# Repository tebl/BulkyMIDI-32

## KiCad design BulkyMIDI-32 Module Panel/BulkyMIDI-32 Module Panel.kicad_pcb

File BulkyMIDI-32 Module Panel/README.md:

# BulkyMIDI-32 Module Panel
This is a front-facing panel for controlling the *BulkyMIDI-32 Module*, while optional by design I find that it makes the system a lot more enjoyable in use and looks better while on my desk.

- [1> Building the device](#1-building-the-device)
  - [1.1> Soldering it together](#11-soldering-it-together)
- [2> Schematic](#2-schematic)
- [3> BOM](#3-bom)

# 1> Building the device
Building a device such as this assumes you have at least minor experience soldering things together, recommended is that you at the very least have access to a soldering station with adjustable temperature. If currently available, you should probably start with 60/40 rosin core solder as the lead-free alternatives tends to be a bit harder to work with.

With requirements for basic equipment sorted, we need to talk a bit about what you want to achieve while building this project. The reason I ask is that while you can build a functional *mt32-pi* using the module alone, you can also build the complete version of it - including front panels, faceplates that goes on the top as well as *extras*-module for additional functionality. 

Now that you know what you want to build, we can get started on the most expensive step in any build process - shopping! So, head on over to the [BOM](#3-bom)-section for some information on what kind of components that you'll need. While I would have liked to give you specific part numbers for "reputable" electronic part suppliers, I can't afford to shop there so I usually make due with what I can find on sites such as ebay, AliExpress and any similar sites that sell cheap chinese components. The downside to this is that I can't link to a part directly and expect it to stay listed, so you'll need to consider the description listed as suggested search terms.

## 1.1> Soldering it together

The construction of this unit should be fairly straight-forward, just take your time in order to make sure everything goes into place - more or less straight. I usually recommend starting by having a good look at the PCBs, try to figure out where all of the listed components go and in which orientation they go in (all of this should be clearly marked on the silkscreen). 

The first component to install might be a bit backwards to normal convention, but I've started wth the 8mm hex standoffs. The hex shape needs to be rotated a flat edge lines up with the left and right edges of the PCB, the reason for this will become evident when we attempt to install it onto the main module. As these are just nylon, I've made things slightly easier for myself by using a sharp knife to trim a bit off the vertical edges of them - in particular the one sitting just above the power LED.

As the next step, I've skipped a bit too far ahead and simply added everything - starting with the right-angle pin headers that will be mounted on the backside of the PCB. The alignment of the remaining components need to be perfectly straight, so my recommendation is to insert them roughly into place then mount the [front plate](https://github.com/tebl/BulkyMIDI-32/tree/main/faceplates/BulkyMIDI-32%20Module%20FP1) on the top of it. A single pin of each component is then soldered, check the alignment and then reheat and adjust as needed. I prefer to push the LED slightly from the back to ensure that it is sitting flush against the front plate.

The front panel would then been removed again, mostly because it'll slightly be in the way when installing it onto the main [BulkyMIDI-32](https://github.com/tebl/BulkyMIDI-32/tree/main/BulkyMIDI-32%20Module) PCB. Before continuing we need to deal with the solder jumbers found on the back, these are divided into two sets of jumpers that need to be added.

The first pair marked **JP1/JP2** control the scroll direction of the rotary encoder, but for the most part you'd just solder both of these across pins *1-2* (the little triangle denotes pin 1). This should be fine for most of the rotary encoders that I've encountered, but in the case that they will appear to work backwards from what you expect - then move the solder bridge to pins *2-3* instead.

Next we need to deal with **JP3/JP4**, these are used to deal with the rather unfortunate situation caused by some manufacturers making changes to the pinout. Particularly this is a problem with 0.96" OLED displays, often you'll order a display based on the picture in the listing and receive a display with a different pinout than that of what you had ordered. The only way around it is to ensure that we handle that on our end of the hardware, for the specific display shown above you can see thet the first pin has been marked *GND* - for that reason we need to solder both jumpers across pins *1-2* (the little triangle denotes pin 1). If on the hand, *VCC* had been the first pin then we would instead need to solder both across pins *2-3*. Preferably double-check and triple-check this before continuing as the wrong setting will commonly destroy the display module.

The actual installation of the display needs to be oriented perfectly against the front panel, but that part of the build details will be handled as part of the [build instructions](https://github.com/tebl/BulkyMIDI-32/blob/main/BulkyMIDI-32%20Module/README.md#132-front-panel) for the [main](https://github.com/tebl/BulkyMIDI-32/tree/main/BulkyMIDI-32%20Module) module.

# 2> Schematic
The supplied KiCad files should be sufficient as both a schematic and as a  starting point for ordering PCBs (basically you could just zip the contents of the export folder and upload that on a fabrication site), the schematic is also available in [PDF-format](https://github.com/tebl/BulkyMIDI-32/tree/main/documentation/schematic) and this is what you'll need to print and work your way through this things don't work as expected after assembly.

# 3> BOM
Most parts should be easy to get a hold of from your favourite local electronic component shop, but given that I don't have access to such shops where I live so everything was based on whatever I could get cheapest from eBay/AliExpress (free shipping, but plan on waiting 3-4 weeks for delivery). Components in parenthesis can be considered optional for features beyond the more basic functionality, but where's the fun in that? You deserve the complete package.

| Reference             | Item                                                              | Count | Order  |
| --------------------- | ----------------------------------------------------------------- | ----- | ------ |
| Panel PCB             | Fabricate using Gerber files                                      |     1 | [PCBWay](https://www.pcbway.com/project/shareproject/BulkyMIDI_32_Module_Panel_17b7fa7c.html)
| D1                    | 5mm LEDs, preferably frosted (not the bright clear ones)          |     1 |
| ENC1                  | EC11 rotary encoder, 20mm. Preferably plum handle                 |     1 |
| IC1                   | 1.3 inch I2C OLED display (can use 0.96 inch display as well)     |     1 |
| J1                    | Breakable right-angle pin header                                  |     1 |
| SW1,SW2               | 6x6x12mm momentary button                                         |     2 |
| Mounting ****         | Nylon M3 hex standoffs 8mm (M-F)                                  |     4 |
| Mounting ****         | Nylon M3x6mm nylon screws                                         |     4 |
| Mounting ****         | Nylon M3x6mm nylon nuts                                           |     4 |

****) These are available in the form of kits usually advertised *M3 nylon standoff kit* which should contain most of what you'd need. I do however recommend that you pick up extra M-F standoffs of lengths 8mm and 20mm, as quite a lot of them will be used when building more than one module.

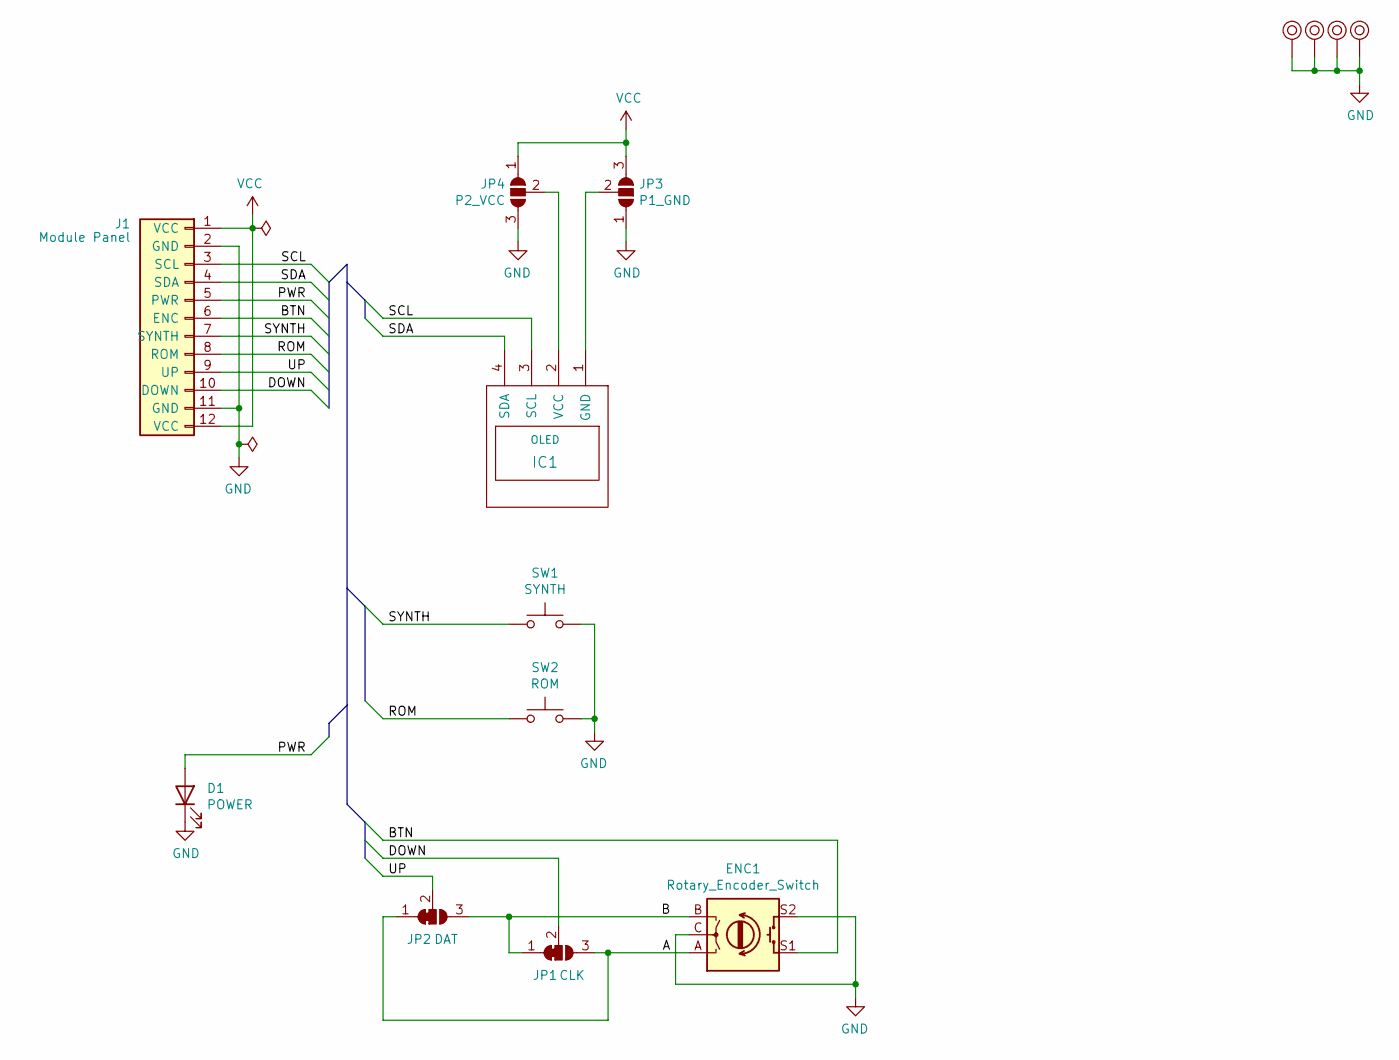
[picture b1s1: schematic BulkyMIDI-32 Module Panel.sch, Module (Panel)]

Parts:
D1: POWER; LED_D5.0mm
ENC1: Rotary_Encoder_Switch; RotaryEncoder_Alps_EC11E-Switch_Vertical_H20mm
IC1: OLED; 1.3_I2C_OLED_No_mounting
J1: Module Panel; PinHeader_1x12_P2.54mm_Horizontal
JP1: CLK; SolderJumper-3_P1.3mm_Open_Pad1.0x1.5mm
JP2: DAT; SolderJumper-3_P1.3mm_Open_Pad1.0x1.5mm
JP3: P1_GND; SolderJumper-3_P1.3mm_Open_Pad1.0x1.5mm
JP4: P2_VCC; SolderJumper-3_P1.3mm_Open_Pad1.0x1.5mm
M1, M2, M3, M4: Mounting_Pin; M3_pin
SW1: SYNTH; SW_PUSH_6mm
SW2: ROM; SW_PUSH_6mm

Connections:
/A: ENC1.A, JP1.3 (B), JP2.1 (A)
/B: ENC1.B, JP1.1 (A), JP2.3 (B)
/BTN: ENC1.S1, J1.6 (ENC)
/DOWN: J1.10 (DOWN), JP1.2 (C)
/PWR: D1.2 (A), J1.5 (PWR)
/ROM: J1.8 (ROM), SW2.1
/SCL: IC1.3 (SCL), J1.3 (SCL)
/SDA: IC1.4 (SDA), J1.4 (SDA)
/SYNTH: J1.7 (SYNTH), SW1.1
/UP: J1.9 (UP), JP2.2 (C)
GND: D1.1 (K), ENC1.C, ENC1.S2, J1.2 (GND), J1.11 (GND), JP3.1 (A), JP4.3 (B), M1.1, M2.1, M3.1, M4.1, SW1.2, SW2.2
unnamed: IC1.1 (GND), JP3.2 (C)
unnamed: IC1.2 (VCC), JP4.2 (C)
VCC: J1.1 (VCC), J1.12 (VCC), JP3.3 (B), JP4.1 (A)

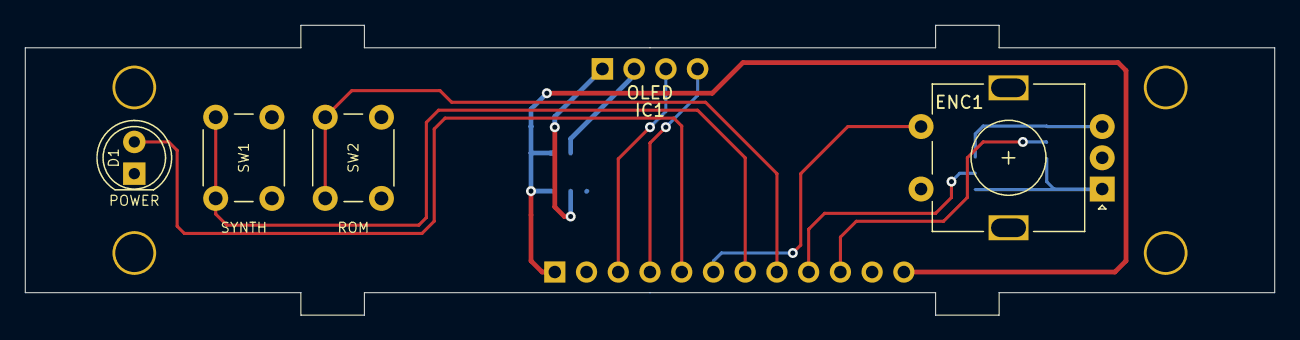
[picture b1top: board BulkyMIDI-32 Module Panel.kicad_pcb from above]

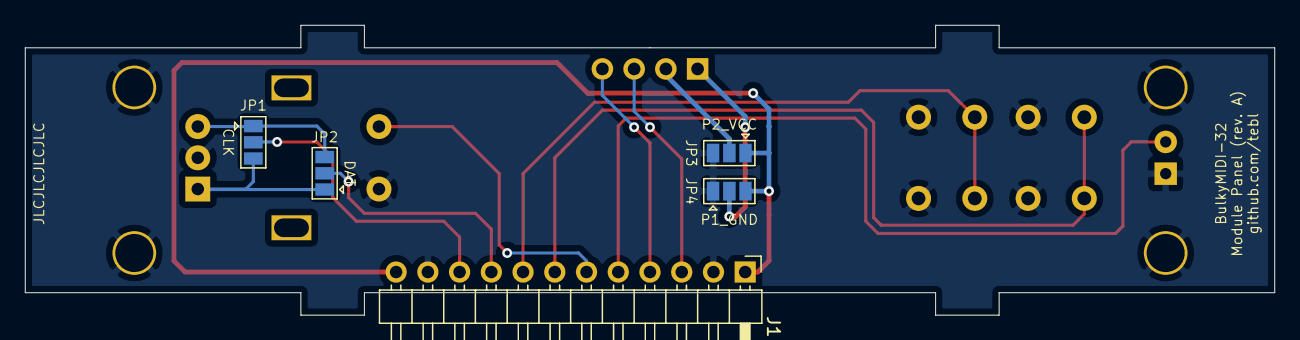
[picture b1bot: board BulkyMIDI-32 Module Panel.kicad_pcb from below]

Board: 2 copper layers, 100.0 x 23.2 mm, 14 parts (5 on the bottom side), 14 nets.

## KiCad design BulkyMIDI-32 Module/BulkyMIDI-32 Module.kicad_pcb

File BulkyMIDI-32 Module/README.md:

# BulkyMIDI-32 Module
The complete BulkyMIDI-32 consists of several separate PCB designs, this documentation covers the main module that enables you to use common functionality supported by the [mt32-pi](https://github.com/dwhinham/mt32-pi) firmware. Any additional modules such as the [BulkyMIDI-32 Extras](https://github.com/tebl/BulkyMIDI-32/tree/main/BulkyMIDI-32%20Extras), will have their own set of documenentation - so make sure that you browse around to get the full picture (especially while ordering parts).

- [1> Building the device](#1-building-the-device)
  - [1.1> Soldering it together](#11-soldering-it-together)
  - [1.2> I2S DAC](#12-i2s-dac)
  - [1.3> User interface](#13-user-interface)
    - [1.3.1> Basic interface](#131-basic-interface)
      - [1.3.1.1> Mounting the screen](#1311-mounting-the-screen)
    - [1.3.2> Front panel](#132-front-panel)
  - [1.4> Adding connectors](#14-adding-connectors)
  - [1.5> Finishing touches](#15-finishing-touches)
- [2> Schematic](#2-schematic)
- [3> BOM](#3-bom)

# 1> Building the device
Building a device such as this assumes you have at least minor experience soldering things together, recommended is that you at the very least have access to a soldering station with adjustable temperature. If currently available, you should probably start with 60/40 rosin core solder as the lead-free alternatives tends to be a bit harder to work with.

With requirements for basic equipment sorted, we need to talk a bit about what you want to achieve while building this project. The reason I ask is that while you can build a functional *mt32-pi* using the module alone, you can also build the complete version of it - including front panels, faceplates that goes on the top as well as *extras*-module for additional functionality. 

Now that you know what you want to build, we can get started on the most expensive step in any build process - shopping! So, head on over to the [BOM](#3-bom)-section for some information on what kind of components that you'll need. While I would have liked to give you specific part numbers for "reputable" electronic part suppliers, I can't afford to shop there so I usually make due with what I can find on sites such as ebay, AliExpress and any similar sites that sell cheap chinese components. The downside to this is that I can't link to a part directly and expect it to stay listed, so you'll need to consider the description listed as suggested search terms.

While you wait for the parts to arrive, feel free to have a look at the introduction video - going into what the Roland MT-32 is and why you would want one. Also covers MIDI and where the MT32-PI software comes into all of this. 

## 1.1> Soldering it together
The construction of this unit should be fairly straight-forward, just take your time in order to make sure everything goes into place - more or less straight. To aid you in the process I've put together a video showing most of these parts in detail, but feel free to skip forward to the various chapters if you feel unsure about things.

I usually recommend starting by having a good look at the PCBs, try to figure out where all of the listed components go and in which orientation they go in (all of this should be clearly marked on the silkscreen). 

I will usually try to install components sorted by their physical size, doing it this way means you'll have an easier time keeping everything from looking somewhat crooked. This is your board, your build and you want it perfect - don't you? If you said no, then go sit in the corner because I worked hard on creating this for myself and whoever wants to build one.

Here we've started by soldering all of the resistors, ensuring that we're using the correct values in each position. The single 1n4148 diode has also been installed, pay particular attention that the black band of the components matches up with the markings on the PCB.

Sockets should be installed for the two ICs needed for the complete unit - you could probably manage without them if you know that you're using known good parts. However, they're cheap and you could probably afford to be quite so *cheap*!  I recommend tacking opposing corners into place, then reheat and push flush against the board before soldering the remaining pins.

We've also gone ahead and installed our non-polarized capacitors - they should in theory be something called an *X7R* or *film* capacitors. I don't have any of those, so I just used the regular stuff I have around the workshop instead (it'll be fine - I probably wouldn't be able to tell the difference anyway).  

Next step is adding the female 40-pin header, this is where we'll be plugging in our Raspberry Pi 3 or 4 - sometime in the future.

Speaking of capacitors, we'll just go ahead and install the polarized ones as well - of which, there are 10 (unless my counting is *off* or outdated, that's two in binary). As polarized as they are, we need to ensure that these are installed the right way around - the stripe on the side of the capacitor denotes the negative side of it (not the correct term I fear) and this should match the filled in area on the footprint. When in doubt, the longer pin goes into the other hole (the one marked with a "+").

Also added is your common DC barrel connector (5.5mm x 2.1mm), these are notorious for going in crooked so make sure to only solder one pin to get started. Reheat and adjust until perfectly satisfied with the result, then solder in the remaining pins before continuing.

## 1.2> I2S DAC
If you've ever attempted to use a Raspberry Pi module as some sort of desktop solution, you may already have noticed the rather horrible audio quality coming out of its audio jack. For this reason alone, we need to include a separate DAC as part of the design. While there are a few variants on sale, the one that is compatible with this design is listed as a *GY-PCM5102*-module - commonly found on ebay, AliExpress and places known for cheap components. When in doubt, look for the colour purple among when the store listings.

There are a set of solder jumpers on the underside, you need to check that these are set up according to what is shown above. These'll be inaccessible after solder the modules together, so this is definitely the time for checking it twice. H3L should be linked in the left position, the remaining in the right position. I've also gone ahead and added the pin headers to the board.

Here we've just gone ahead and soldered it to the main board. On the underside there are some solder bridges that can be added, these'll send the analog audio signal to the extras board connector. Personally I just solder them so that they're ready for the extras board - sound aficionados may appreciate the option not to, but again I just wasn't able to detect any difference.

## 1.3> User interface
The user interface can be added to the *BulkyMIDI-32* in several ways though at the moment only two variants will be covered. The first one, covering basic interface functionality, is intended for putting together a cheaper version - only requiring this module. The second is the more stylish and feature-complete version of the *BulkyMIDI-32*, this mounts all of the buttons as well as the display on a separate [front panel](https://github.com/tebl/BulkyMIDI-32/tree/main/BulkyMIDI-32%20Module%20Panel)-module. 

- [1.3.1> Basic interface](#131-basic-interface)
  - [1.3.1.1> Mounting the screen](#1311-mounting-the-screen)
- [1.3.2> Front panel](#132-front-panel)

### 1.3.1> Basic interface
**WARNING!** The pictures for this section are outdated, but as long as you follow the descriptions you'll find that although the position of the components have been moved around to put the display in the middle of the device. Despite this, the process should be comparable.

When you want to build a simpler version of the *BulkyMIDI-32*, the switches will be installed directly on the module as one would expect. This configuration requires that you link **SW4_SEL** pins **1-2** on the back of the PCB as well.

**NB!** If you've already built a previous version of the [extras](https://github.com/tebl/BulkyMIDI-32/tree/main/BulkyMIDI-32%20Extras)-board the separate adapter board for the rotary encoder, then you can choose to skip the installation of *volume up* and the *volume down* switches.

#### 1.3.1.1> Mounting the screen
For this project you can use the standard 0.96 inch I2C OLED displays available from just about anyone who peddles in Arduino modules, but as a I wanted a bit more flair I instead opted to install a 1.3 inch display. They have a mostly compatible display chip driving it, offering the same amount of pixels - each pixel is just slightly bigger.

**WARNING!** One thing you need to take note of is the organization of the pins, in this case GND is pin 1. Especially the 0.96 inch displays seems to randomly come with the GND and VCC pins swapped around, meaning that if you're not careful - you'll easily destroy the display! We'll cover all of that though, so no worries as long as you follow the instructions.

It's not all that easy to spot in this picture as the display was recycled from an earlier project of mine, but the key to accurately mounting the display somewhat straight is that I've used the long variety of pin headers - they're made of a softer metal and easily bent into the correct position for the display. As some of the backing will be sitting up almost up against the Raspberry Pi, I've added some tape to the back as well in order to avoid any unintended accidents.

Remember when I mentioned earlier about wiring up the display correct? This is where you do that. When viewed from the front, the display pictured has GND as the first pin. To wire up this correctly, there are a couple of solder bridges near the display connector that we need to link correctly. Given this display, we short across pins **1-2** (the little arrow marking pin 1) for the both of them. If on the other hand, you had VCC as the first pin - then you'd instead link pins **2-3**.

If you've chosen to build a basic unit with the faceplate, then this is probably a good time to get that installed on there - mainly as it'll act as a guide when mounting the display. Turning the display upside down as pictured, insert the pins into the holes and gently bend the pins until you get an orientation that looks somewhat straight. Solder the outside pins into place, reheat and reorient the display until you're happy with the end result. Solder into place the two remaining pins before continuing.

### 1.3.2> Front panel
This section assumes that you've chosen to install a front panel for use with the *BulkyMIDI-32*, this is a bit more advanced way of installing the components for the user interface (switches, OLED-screen and rotary encoder). Building up the [front panel](https://github.com/tebl/BulkyMIDI-32/tree/main/BulkyMIDI-32%20Module%20Panel) in details will be covered by its own documentation, but as it is closely designed for use with this module - some of the information may be duplicated between the two documents. 

A front panel that has been prepared for installing on the module is shown above, in particular you should note that a display has not yet been installed. The reason for this is that we need to get the alignment correct.

Looking at the front panel you've probably noticed that there are some tabs sticking out, these have been designed so that they slot into the main module as well as the faceplates that go on top. The purpose of these is so that every time you're pressing the buttons, you aren't simply bending a comparatively weak set of pin headers that'll be poking through the board. Without soldering anything, insert it into place and fix the faceplate temporarily into place.

If it feels like any of the boards want to bend or not sit straight, check the alignment of the hex standoffs so that they match you can barely see in the picture above. The clue here is that the two sets of standoffs, both the horizontal and the vertical ones need to have a flat side towards eachother - depending on the production of the components you may need to shave a bit off the edge pointing directly up and down to give them a bit more room. I had some issues where the tabs lacked a sharp edge and was binding against the cutout in the boards, these can be cleaned up using a sharp knife (in particular I had this issue when it was produced by JLCPCB as compared to PCBWay). When satisfied with the alignment, you can finally solder the two boards together.

I'm not going to cover the installation of the display in great details, as that would be duplicating a significant portion of the documentation for the [front panel](https://github.com/tebl/BulkyMIDI-32/tree/main/BulkyMIDI-32%20Module%20Panel). In particular there are couple of solder bridges on the back that need to be set up correctly to match the display you're using. Not paying attention to this step will kill your display, at best it simply won't work.

The display should have had some standard pin headers added to them, then simply insert the pins into the front panel without soldering. Add the [front panel faceplate](https://github.com/tebl/BulkyMIDI-32/tree/main/faceplates/BulkyMIDI-32%20Module%20FP1) using screws, allowing the display to flop around between the two front panel boards. Orient the display as correctly as you can, then solder one of the pins into place - reaheat and move it around as needed until you're happy with it it - the display should be straight when viewed from the front window, it should also be mostly flush against it. Solder the remaining pins to finish the installation.

## 1.4> Adding connectors
The number of connectors needed would depend on what you want, but I recommend adding both of the 5-pin DIN connectors to the board - the left one is used with data into the device, more than likely this is either your computer with a suitable MIDI-adapter or a keyboard. The right one is for MIDI-output from the device, mostly when you want to chain it to other MIDI-devices.

One slightly annoying part of using these female connectors with the Raspberry Pi is that the height between the two boards will be around 11mm, which is mainly just a problem because I've not seen a vendor selling a cheap one that is this height (plenty of 8mm, 10mm and 12mm standoffs to go around). We could simply just leave it hanging there, but with the prices of these boards we can't do that. Not even close. Luckily, the standoffs have just about enough of a screw on them so that we can add an m3 nut to an 8mm hex standoff and end up with 11mm. Install two of them in the Raspberry Pi mounting holes and now we have something for it to rest on.

The picture should resemble what you've built so far, depending somewhat on the option you chose for the user interface (the version with front panel is shown).

## 1.5> Finishing touches
If you've made it this far, you should hopefully be ready to start using it. Check out the additional documentation for [setting it up](https://github.com/tebl/BulkyMIDI-32/blob/main/documentation/setting_it_up.md), mainly taking care of setting up your memory with the configuration to match the hardware you've just built. [Getting started](https://github.com/tebl/BulkyMIDI-32/blob/main/documentation/getting_started.md) goes through some of the low-hanging fruits when it comes to actually playing music through it.

The device is powered using a 5v DC barrel jack (center positive) with sufficient amperage to support the version of the Raspberry Pi module you are using. These should be easy to obtain from your favourite electronics vendor, just make sure that it's from a somewhat respected brand.

The Raspberry Pi 4 is significantly slower to boot than their previous generation, so give it a few more seconds before panicking - you should get something on your I2C screen after a short while. If you don't, remove the Raspberry Pi and connect it to HDMI and see if it looks the boot screen changes with or without the memory card inserted (MT32-PI doesn't generate a picture, but it'll be different from not being able to boot such as when a memory card is unavailable or unbootable). You should also doublecheck that you set up the [configuration](https://github.com/tebl/BulkyMIDI-32/blob/main/documentation/setting_it_up.md) to match the type of display you are using or its address may have been set differently.

If you intend to use the BulkyMIDI-32 along with [BulkyMIDI-32 Extras](https://github.com/tebl/BulkyMIDI-32/tree/main/BulkyMIDI-32%20Extras), now is a good time to get started on following the build instructions for building up one of those as well. Interconnecting them vertically is done using some extra length female pin headers on the extras board and some simple dual row pin-headers on the underside of this board. The board acts as an expansion, adding several of the features and options that I could not easily fit within the main boards dimensions. If you need MIDI THRU ports, passive audio mixing as well as one or two RS232-module or wanted to use a rotary encoder then that's where you'll find these options.

# 2> Schematic
The supplied KiCad files should be sufficient as both a schematic and as a  starting point for ordering PCBs (basically you could just zip the contents of the export folder and upload that on a fabrication site), the schematic is also available in [PDF-format](https://github.com/tebl/BulkyMIDI-32/tree/main/documentation/schematic) and this is what you'll need to print and work your way through this things don't work as expected after assembly.

# 3> BOM
Most parts should be easy to get a hold of from your favourite local electronic component shop, but given that I don't have access to such shops where I live so everything was based on whatever I could get cheapest from eBay/AliExpress (free shipping, but plan on waiting 3-4 weeks for delivery). Components in parenthesis can be considered optional for features beyond the more basic functionality, but where's the fun in that? You deserve the complete package.

| Reference             | Item                                                              | Count | Order  |
| --------------------- | ----------------------------------------------------------------- | ----- | ------ |
| BulkyMIDI-32 Module   | Fabricate using Gerber files                                      |     1 | [PCBWay](https://www.pcbway.com/project/shareproject/BulkyMIDI_32_35d2ed18.html)
| A1                    | 2x20 pin female header                                            |     1 |
|                       | Raspberry Pi version 3 or 4                                       |     1 |
| A2                    | GY-PCM5102 I2S DAC (the purple kind)                              |     1 |
| C1,C3,C4              | 100nF ceramic capacitor (5mm)                                     |     3 |
| C5                    | 100uF electrolytic capacitor (6.3mm x 2.5mm)                      |     1 |
| C6                    | 470uF electrolytic capacitor (8mm x 3.5mm)                        |     1 |
| D1                    | 1N4148N small signal diode (DO-35)                                |     1 |
| ENC1                  | 5-pin right angle pin header                                      |    (1)|
| IC1 *2                | 1.3 inch I2C OLED display (can use 0.96 inch display as well)     |     1 |
| J1                    | 2.1mm x 5.5mm barrel plug                                         |     1 |
| J2, J3                | Female S-terminal 5pin DIN PCB                                    |     2 |
| J5                    | 5-pin right angle pin header                                      |    (1)|
| J6                    | 4-pin right angle pin header                                      |    (1)|
| J7                    | 2x10 pin header (mounted on underside for extras board)           |    (1)|
| R1,R2,R4,R5,R6        | 220 ohm resistor                                                  |     5 |
| R3                    | 1k ohm resistor                                                   |     1 |
| R7 *1                 | 330 ohm resistor                                                   |   (1)|
| SW1-SW4 *2            | 6x6x5mm right-angle momentary button                              |     4 |
| U1                    | 74HCT14 (DIP-14)                                                  |     1 |
| U2                    | H11L1M opto-coupler (DIP-6)                                       |     1 |
| Mounting *3           | Nylon M3 hex standoffs 20mm (M-F)                                 |     4 |
| Mounting *4           | Nylon M3 hex standoffs 20mm (M-F)                                 |     4 |
| Mounting *3           | Nylon M3 hex standoffs 8mm (M-F)                                  |     6 |
| Mounting *3           | Nylon M3 hex standoffs 12mm (M-F)                                 |     4 |
| Mounting *3           | Nylon M3x6mm nylon screws                                         |     8 |
| Mounting *3           | Nylon M3x6mm nylon nuts                                           |     6 |

1) This is the resistor for the power LED mounted on front-facing panel, the value need to be sized according to the type of LED used. This value is suitable for a red LED of the older type, for any kind of modern component you'll need a value significantly higher (I tend to use 2k2 or 3k3 here depending on the colour).
2) These components are only used when no other PCBs will be used, ie. no front panel.
3) These are used in various places of the project, these are available in the form of kits usually advertised *M3 nylon standoff kit* which should contain most of what you'd need.
4) These are used with a faceplate and are installed on the bottom of the unit. When used with the extras-unit, these will be replaced by another set (4x) of 20mm (M-F) standoffs and another set of nuts to go on the bottom.

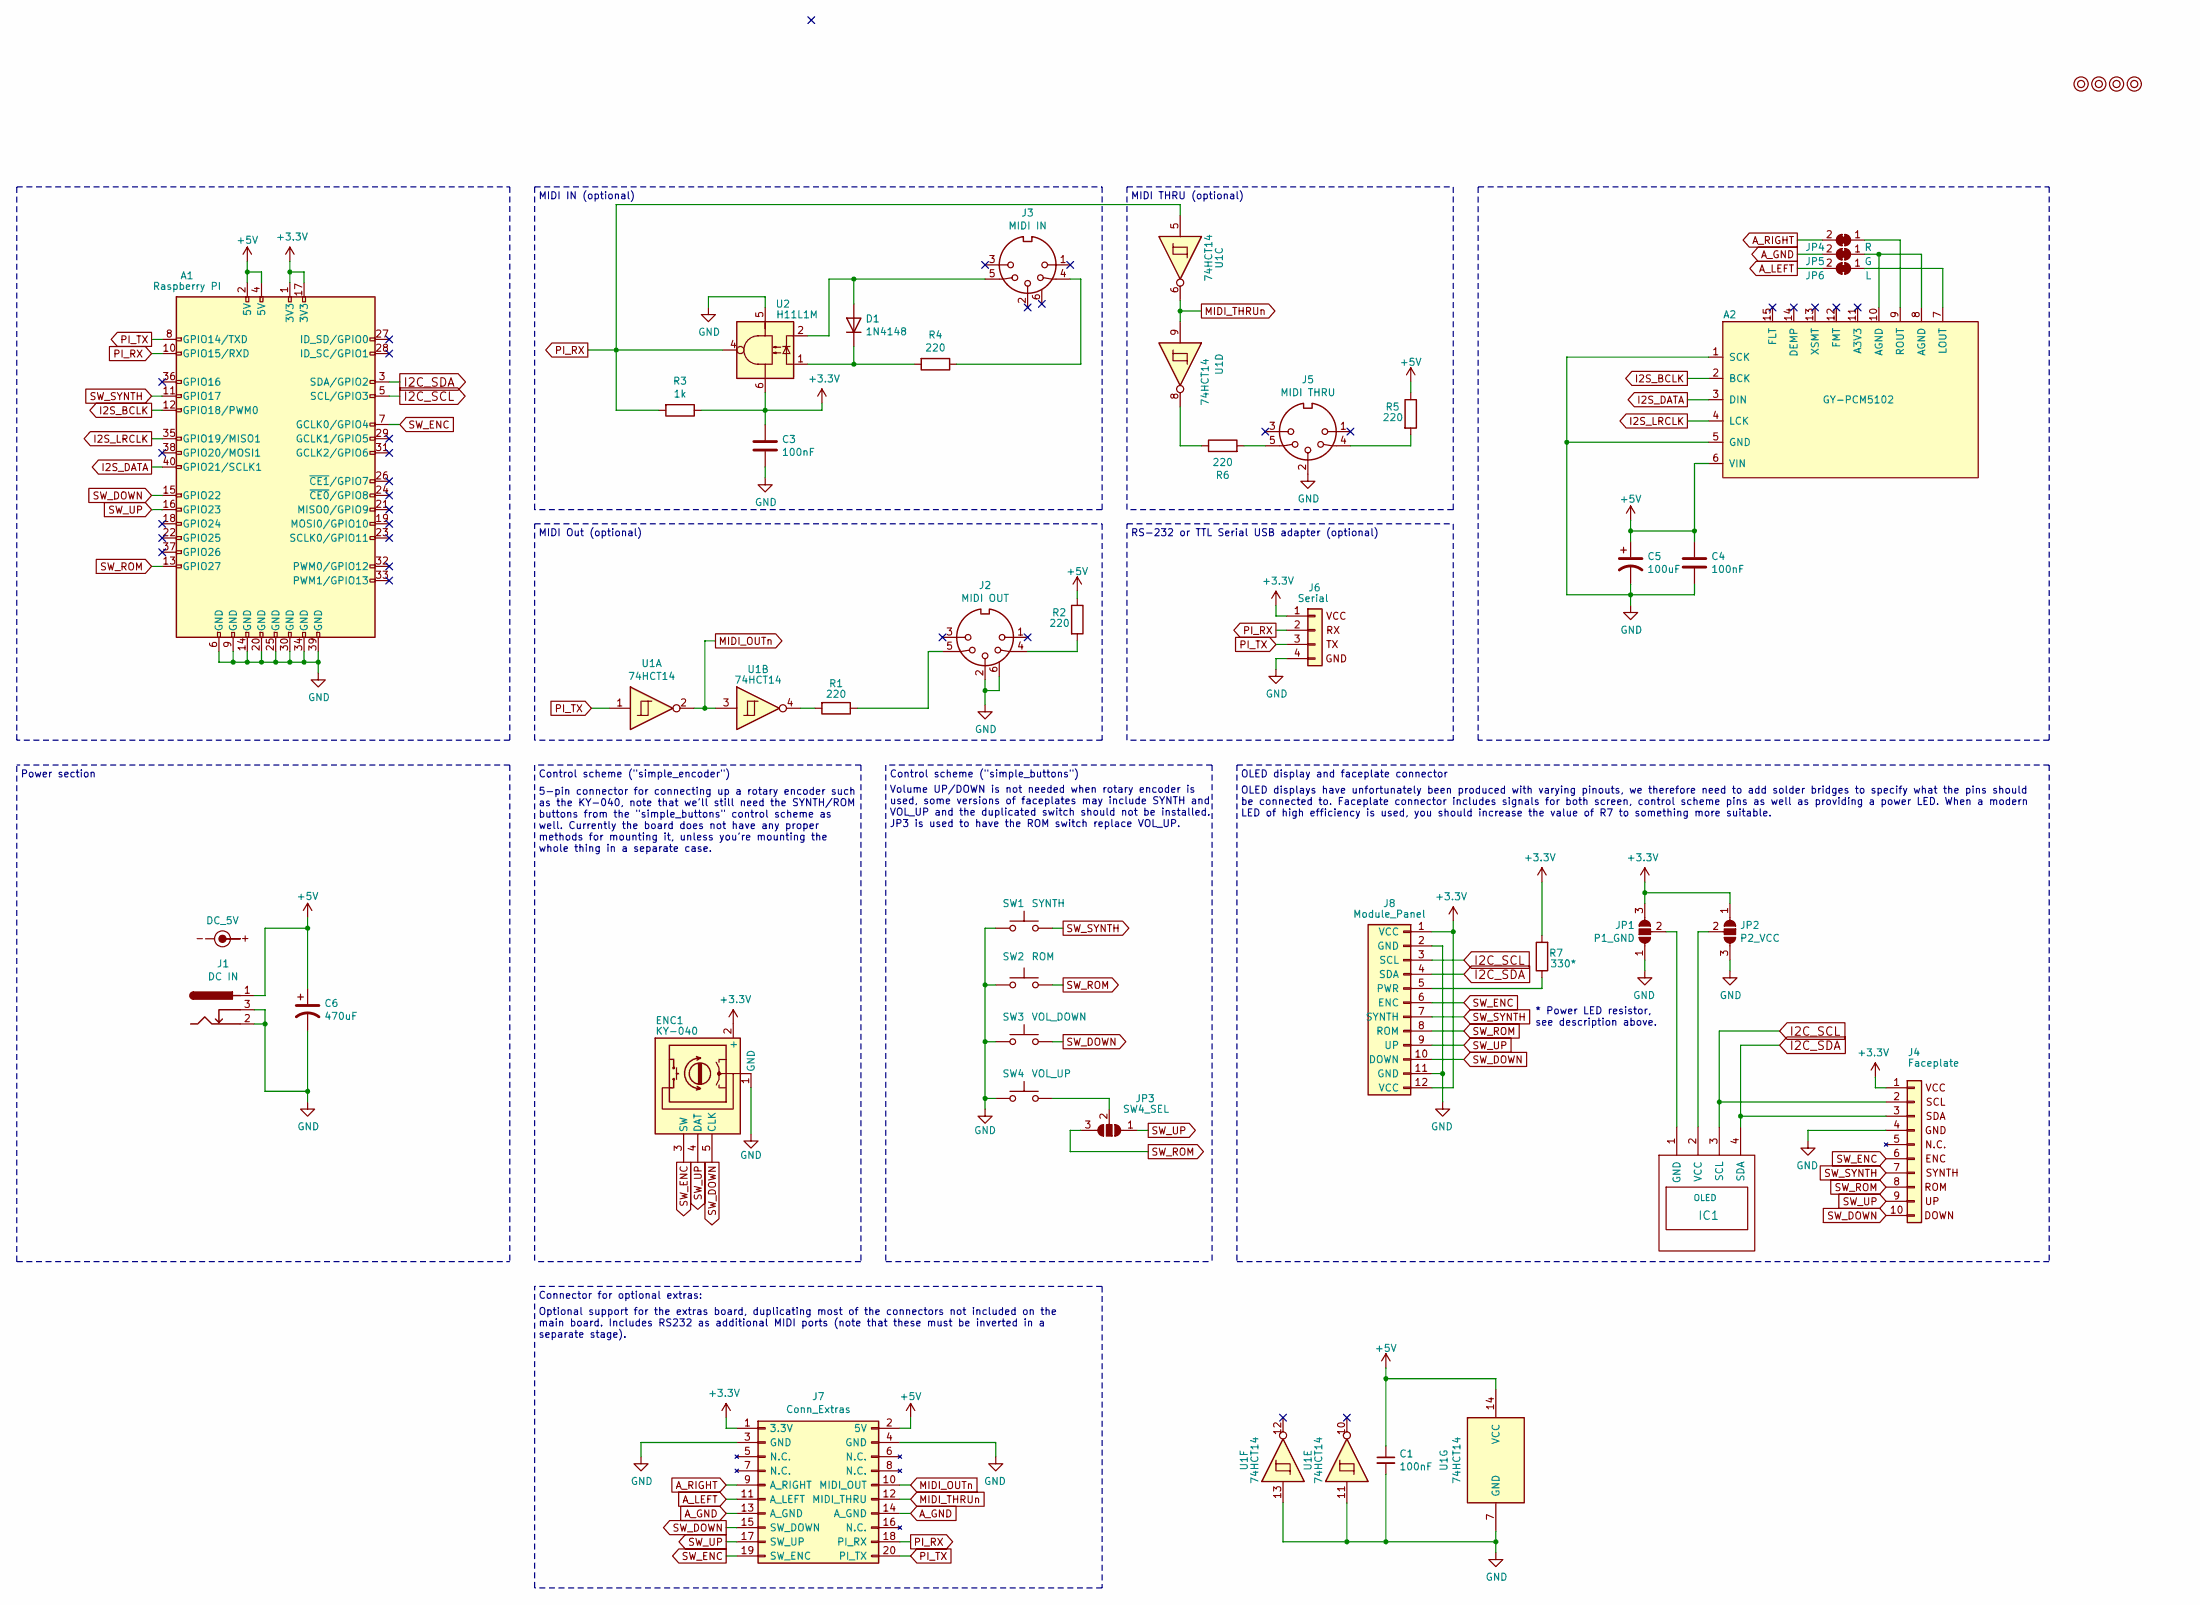
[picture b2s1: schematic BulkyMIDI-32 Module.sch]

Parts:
A1: Raspberry PI; Raspberry_Pi_3B_Socketed_THT_FaceDown_MountingHoles
A2: GY-PCM5102
C1, C3, C4: 100nF; C_Rect_L7.0mm_W2.0mm_P5.00mm
C5: 100uF; CP_Radial_D6.3mm_P2.50mm
C6: 470uF; CP_Radial_D8.0mm_P3.50mm
D1: 1N4148; D_DO-35_SOD27_P7.62mm_Horizontal
ENC1: KY-040; PinHeader_1x05_P2.54mm_Horizontal
IC1: OLED; 1.3_I2C_OLED_No_mounting
J1: DC IN; BARREL_JACK
J2: MIDI OUT; DIN5_MIDI_OUT
J3: MIDI IN; DIN5_MIDI_IN
J4: Faceplate; PinSocket_1x10_P2.54mm_Vertical
J5: MIDI THRU; PinHeader_1x05_P2.54mm_Horizontal
J6: Serial; PinHeader_1x04_P2.54mm_Horizontal
J7: Conn_Extras; PinSocket_2x10_P2.54mm_Vertical
J8: Module_Panel
JP1: P1_GND; SolderJumper-3_P1.3mm_Open_RoundedPad1.0x1.5mm
JP2: P2_VCC; SolderJumper-3_P1.3mm_Open_RoundedPad1.0x1.5mm
JP3: SW4_SEL; SolderJumper-3_P1.3mm_Open_RoundedPad1.0x1.5mm
JP4: R; SolderJumper-2_P1.3mm_Open_TrianglePad1.0x1.5mm
JP5: G; SolderJumper-2_P1.3mm_Open_TrianglePad1.0x1.5mm
JP6: L; SolderJumper-2_P1.3mm_Open_TrianglePad1.0x1.5mm
M1, M2, M3, M4: Mounting; M3
R1, R2, R4, R5, R6: 220; R_Axial_DIN0207_L6.3mm_D2.5mm_P10.16mm_Horizontal
R3: 1k; R_Axial_DIN0207_L6.3mm_D2.5mm_P10.16mm_Horizontal
R7: 330*; R_Axial_DIN0207_L6.3mm_D2.5mm_P10.16mm_Horizontal
SW1: SYNTH; SW_Tactile_SPST_Angled_PTS645Vx39-2LFS
SW2: ROM; SW_Tactile_SPST_Angled_PTS645Vx39-2LFS
SW3: VOL_DOWN; SW_Tactile_SPST_Angled_PTS645Vx39-2LFS
SW4: VOL_UP; SW_Tactile_SPST_Angled_PTS645Vx39-2LFS
SYM1: DC_5V; PWR_Specification
U1: 74HCT14; DIP-14_W7.62mm
U2: H11L1M; DIP-6_W7.62mm

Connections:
+3V3: A1.1 (3V3), A1.17 (3V3), C3.1, ENC1.2 (+), J4.1 (VCC), J6.1, J7.1 (3.3V), J8.1 (VCC), J8.12 (VCC), JP1.3 (B), JP2.1 (A), R3.1, R7.2, U2.6
+5V: A1.2 (5V), A1.4 (5V), A2.6 (VIN), C1.1, C4.1, C5.1, C6.1, J1.1, J7.2 (5V), R2.1, R5.1, U1.14 (VCC)
A_GND: J7.13 (A_GND), J7.14 (A_GND), JP5.2 (B)
A_LEFT: J7.11 (A_LEFT), JP6.2 (B)
A_RIGHT: J7.9 (A_RIGHT), JP4.2 (B)
GND: A1.6 (GND), A1.9 (GND), A1.14 (GND), A1.20 (GND), A1.25 (GND), A1.30 (GND), A1.34 (GND), A1.39 (GND), A2.1 (SCK), A2.5 (GND), C1.2, C3.2, C4.2, C5.2, C6.2, ENC1.1 (GND), J1.2, J1.3, J2.2, J2.6, J4.4, J5.2, J6.4, J7.3 (GND), J7.4 (GND), J8.2 (GND), J8.11 (GND), JP1.1 (A), JP2.3 (B), SW1.1, SW2.1, SW3.1, SW4.1, U1.7 (GND), U1.11, U1.13, U2.5
I2C_SCL: A1.5 (SCL/GPIO3), IC1.3 (SCL), J4.2, J8.3 (SCL)
I2C_SDA: A1.3 (SDA/GPIO2), IC1.4 (SDA), J4.3, J8.4 (SDA)
I2S_BCLK: A1.12 (GPIO18/PWM0), A2.2 (BCK)
I2S_DATA: A1.40 (GPIO21/SCLK1), A2.3 (DIN)
I2S_LRCLK: A1.35 (GPIO19/MISO1), A2.4 (LCK)
MIDI_OUTn: J7.10 (MIDI_OUT), U1.2, U1.3
MIDI_THRUn: J7.12 (MIDI_THRU), U1.6, U1.9
unnamed: A2.7 (LOUT), JP6.1 (A)
unnamed: A2.9 (ROUT), JP4.1 (A)
unnamed: A2.8 (AGND), A2.10 (AGND), JP5.1 (A)
unnamed: D1.1 (K), R4.2, U2.1
unnamed: D1.2 (A), J3.5, U2.2
unnamed: IC1.1 (GND), JP1.2 (C)
unnamed: IC1.2 (VCC), JP2.2 (C)
unnamed: J2.4, R2.2
unnamed: J2.5, R1.1
unnamed: J3.4, R4.1
unnamed: J5.4, R5.2
unnamed: J5.5, R6.2
unnamed: J8.5 (PWR), R7.1
unnamed: JP3.2 (C), SW4.2
unnamed: R1.2, U1.4
unnamed: R6.1, U1.8
PI_RX: A1.10 (GPIO15/RXD), J6.2, J7.18 (PI_RX), R3.2, U1.5, U2.4
PI_TX: A1.8 (GPIO14/TXD), J6.3, J7.20 (PI_TX), U1.1
SW_DOWN: A1.15 (GPIO22), ENC1.5 (CLK), J4.10 (GND), J7.15 (SW_DOWN), J8.10 (DOWN), SW3.2
SW_ENC: A1.7 (GCLK0/GPIO4), ENC1.3 (SW), J4.6, J7.19 (SW_ENC), J8.6 (ENC)
SW_ROM: A1.13 (GPIO27), J4.8, J8.8 (ROM), JP3.3 (B), SW2.2
SW_SYNTH: A1.11 (GPIO17), J4.7, J8.7 (SYNTH), SW1.2
SW_UP: A1.16 (GPIO23), ENC1.4 (DAT), J4.9, J7.17 (SW_UP), J8.9 (UP), JP3.1 (A)

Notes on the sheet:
MIDI Out (optional)
MIDI THRU (optional)
MIDI IN (optional)
RS-232 or TTL Serial USB adapter (optional)
Control scheme ("simple_buttons")
Power section
OLED display and faceplate connector
OLED displays have unfortunately been produced with varying pinouts, we therefore need to add solder bridges to specify what the pins should be connected to. Faceplate connector includes signals for both screen, control scheme pins as well as providing a power LED. When a modern LED of high efficie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
Volume UP/DOWN is not needed when rotary encoder is used, some versions of faceplates may include SYNTH and VOL_UP and the duplicated switch should not be installed. JP3 is used to have the ROM switch replace VOL_UP.
Connector for optional extras:
Optional support for the extras board, duplicating most of the connectors not included on the main board. Includes RS232 as additional MIDI ports (note that these must be inverted in a separate stage).
Control scheme ("simple_encoder")
5-pin connector for connecting up a rotary encoder such as the KY-040, note that we'll still need the SYNTH/ROM buttons from the "simple_buttons" control scheme as well. Currently the board does not have any proper methods for mounting it, unless you're mounting the whole thing in a separate case.
* Power LED resistor, see description above.

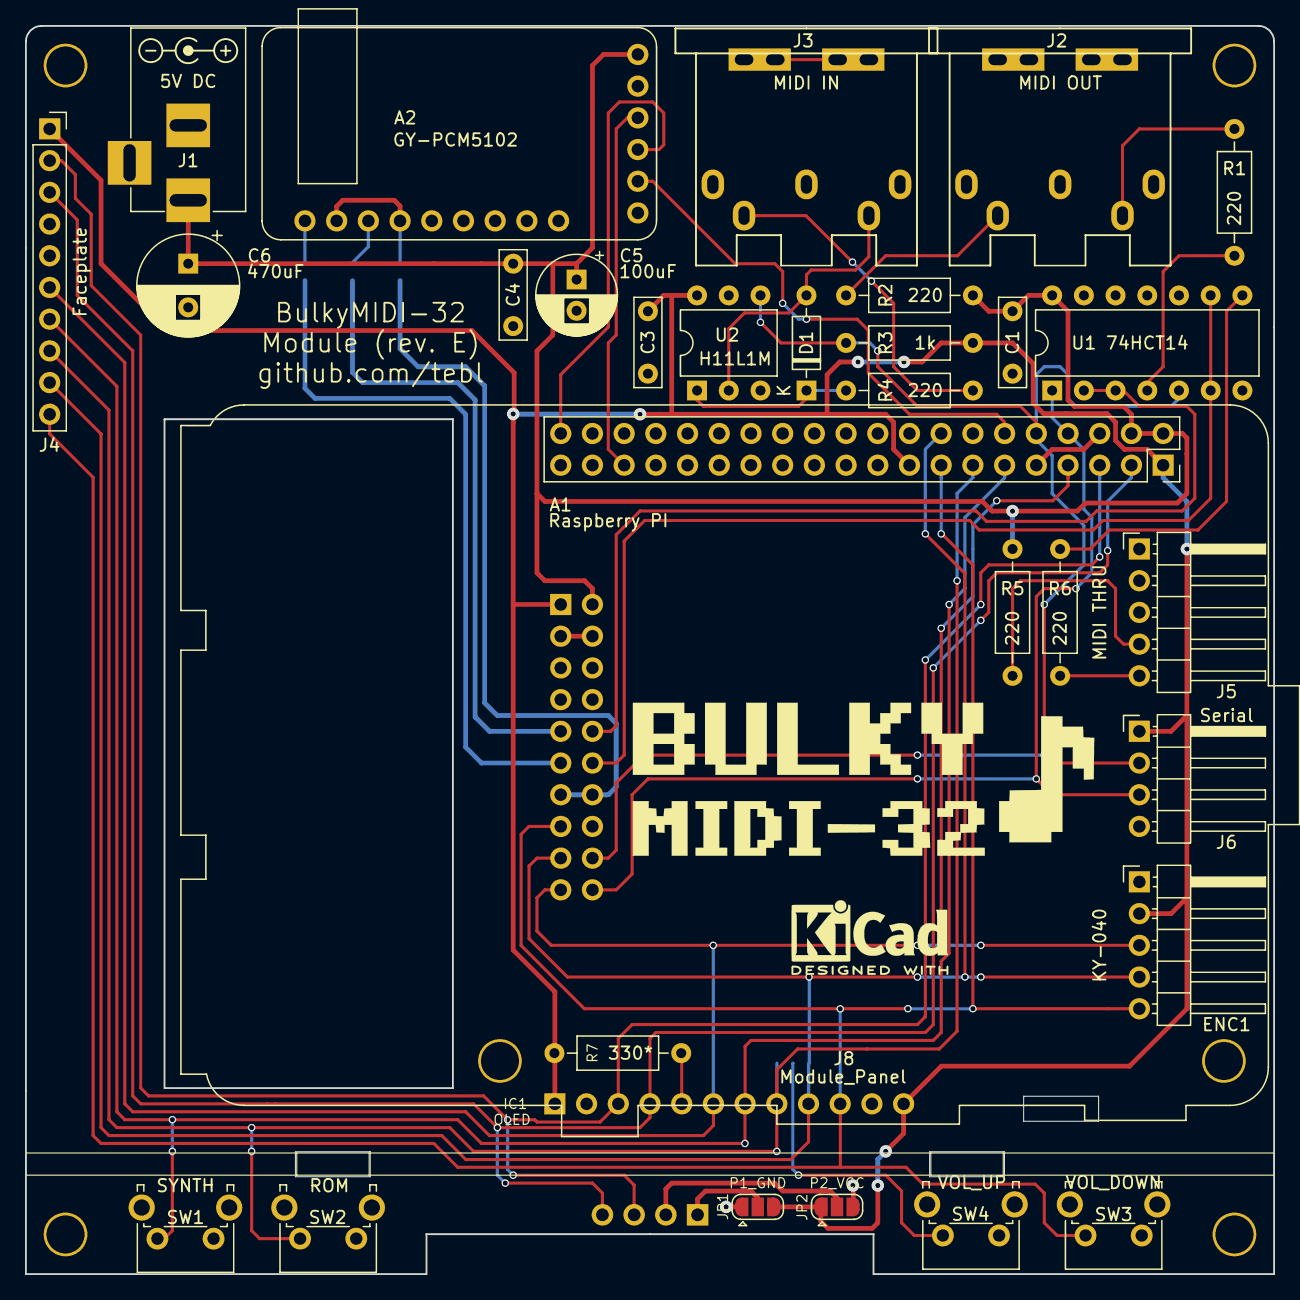
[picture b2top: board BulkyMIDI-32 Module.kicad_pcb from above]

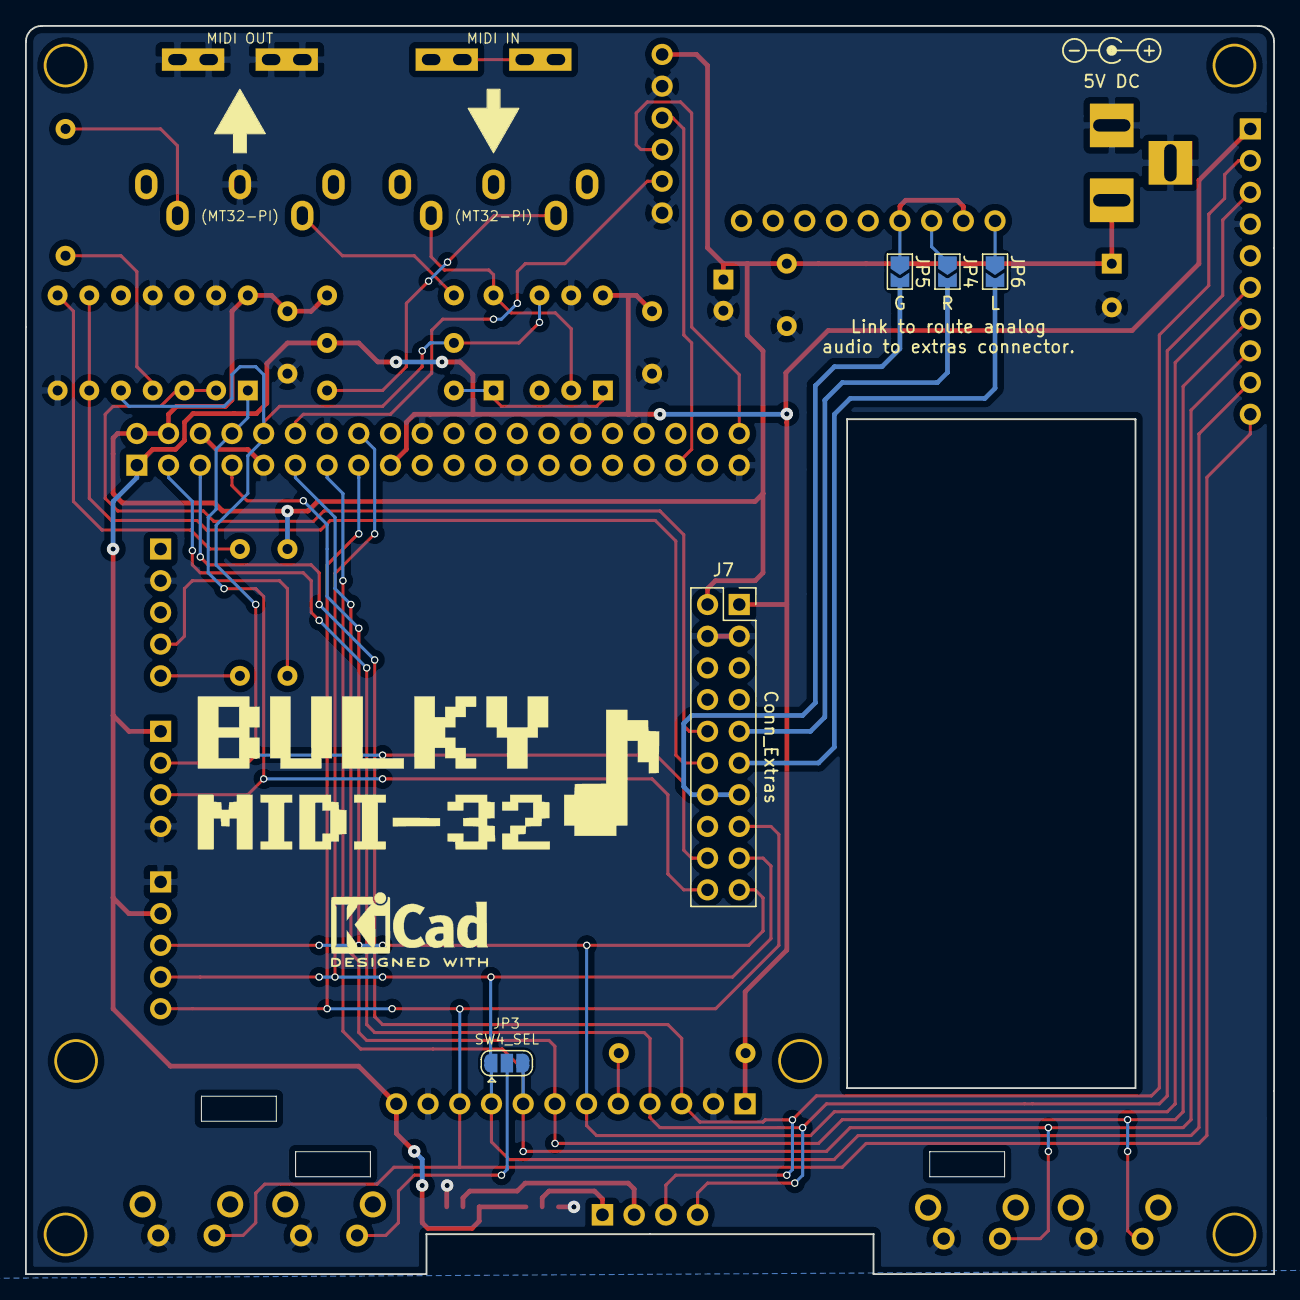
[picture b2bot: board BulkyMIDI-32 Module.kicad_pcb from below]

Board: 2 copper layers, 100.0 x 100.0 mm, 42 parts (5 on the bottom side), 36 nets.

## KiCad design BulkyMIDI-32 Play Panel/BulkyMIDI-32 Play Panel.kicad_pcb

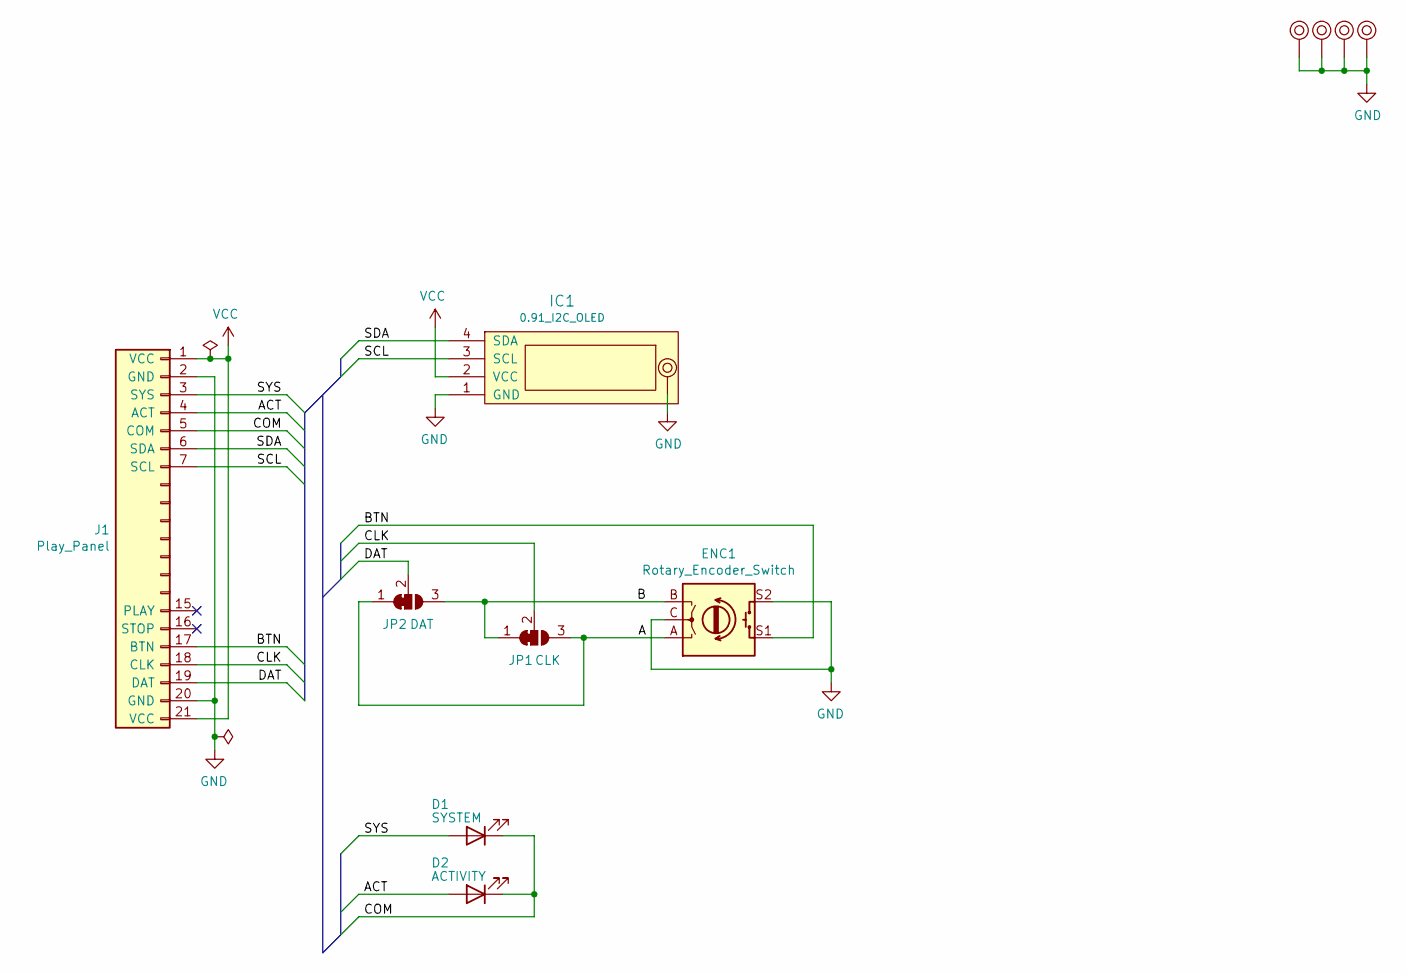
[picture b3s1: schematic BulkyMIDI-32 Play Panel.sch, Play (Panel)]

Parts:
D1: SYSTEM; LED_D5.0mm
D2: ACTIVITY; LED_D5.0mm
ENC1: Rotary_Encoder_Switch; RotaryEncoder_Alps_EC11E-Switch_Vertical_H20mm
IC1: 0.91_I2C_OLED
J1: Play_Panel; PinHeader_1x21_P2.54mm_Horizontal
JP1: CLK; SolderJumper-3_P1.3mm_Open_Pad1.0x1.5mm
JP2: DAT; SolderJumper-3_P1.3mm_Open_Pad1.0x1.5mm
M1, M2, M3, M4, M5: Mounting_Pin; M3_pin

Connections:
/A: ENC1.A, JP1.3 (B), JP2.1 (A)
/ACT: D2.2 (A), J1.4 (ACT)
/B: ENC1.B, JP1.1 (A), JP2.3 (B)
/BTN: ENC1.S1, J1.17 (BTN)
/CLK: J1.18 (CLK), JP1.2 (C)
/COM: D1.1 (K), D2.1 (K), J1.5 (COM)
/DAT: J1.19 (DAT), JP2.2 (C)
/SCL: IC1.3 (SCL), J1.7 (SCL)
/SDA: IC1.4 (SDA), J1.6 (SDA)
/SYS: D1.2 (A), J1.3 (SYS)
GND: ENC1.C, ENC1.S2, IC1.1 (GND), J1.2 (GND), J1.20 (GND), M1.1, M2.1, M3.1, M4.1, M5.1
VCC: IC1.2 (VCC), J1.1 (VCC), J1.21 (VCC)

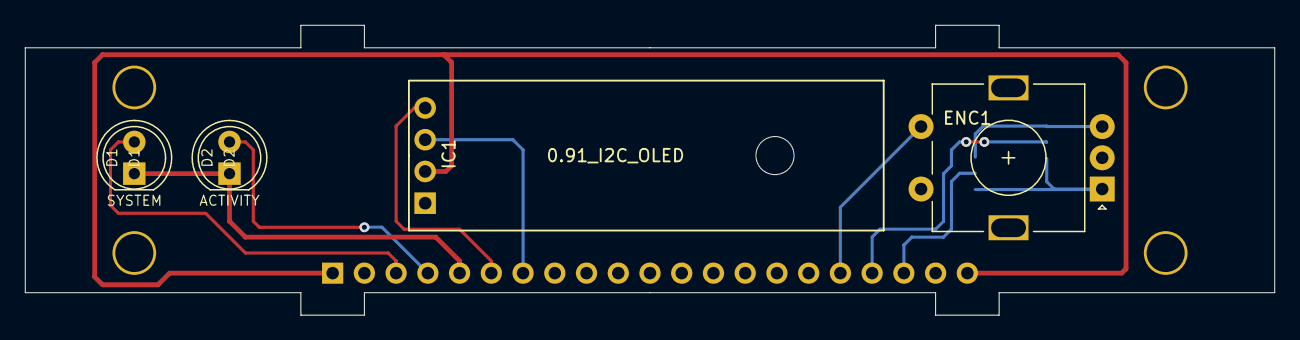
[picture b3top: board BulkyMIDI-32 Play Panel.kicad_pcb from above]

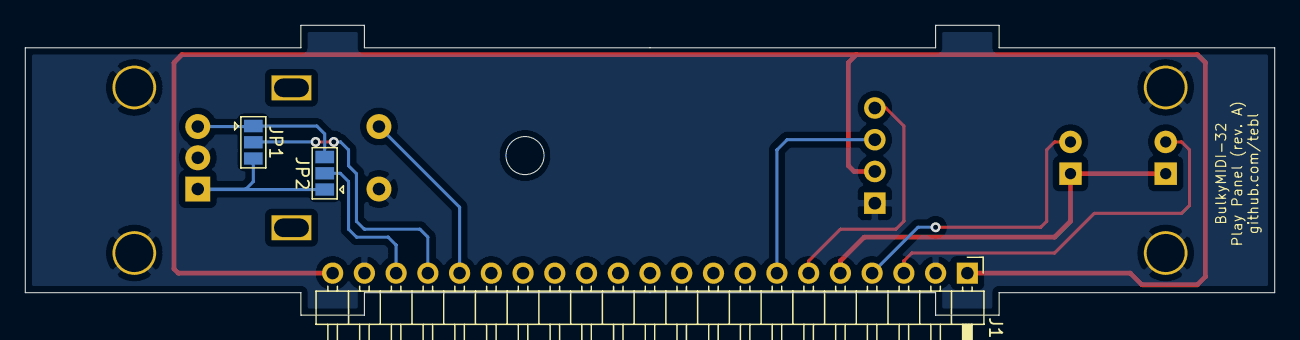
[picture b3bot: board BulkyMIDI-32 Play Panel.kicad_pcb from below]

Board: 2 copper layers, 100.0 x 23.2 mm, 11 parts (3 on the bottom side), 12 nets.
